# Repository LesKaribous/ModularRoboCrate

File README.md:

# ModularRoboCrate

Caisse de stockage et de déplacement pour nos robots et matériel de robotique. Rangements intérieur basés sur le système [GridFinity](https://gridfinity.xyz).

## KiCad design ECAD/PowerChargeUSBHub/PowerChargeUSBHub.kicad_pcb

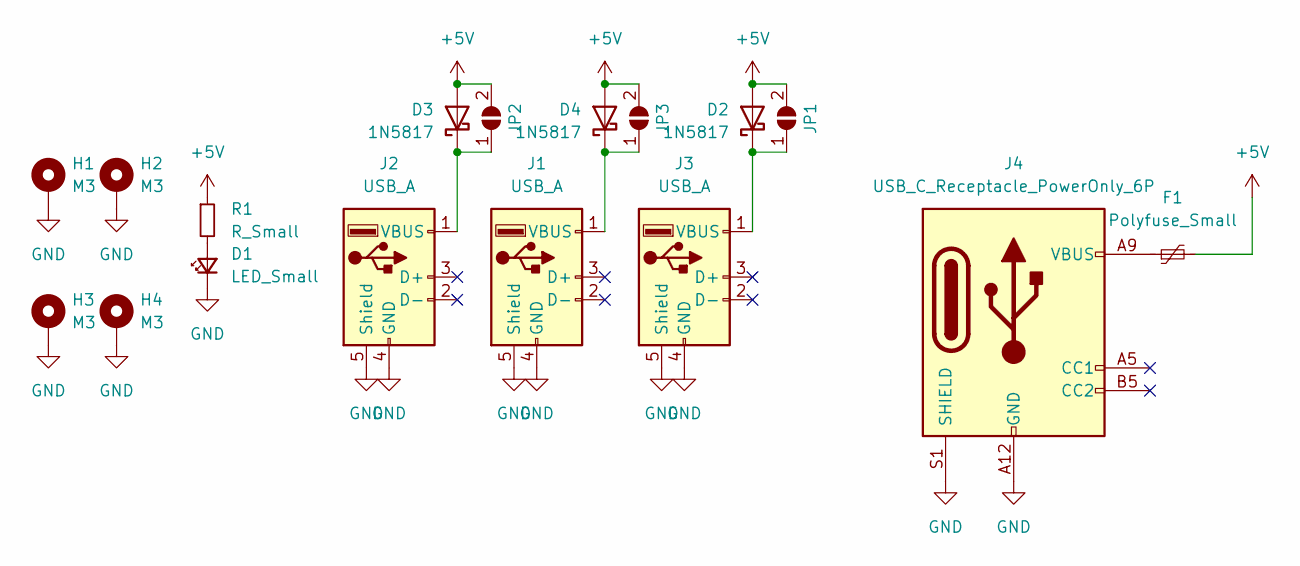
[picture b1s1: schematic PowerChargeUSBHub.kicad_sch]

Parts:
D1: LED_Small; LED_D5.0mm_Horizontal_O1.27mm_Z3.0mm
D2, D3, D4: 1N5817; D_DO-41_SOD81_P10.16mm_Horizontal
F1: Polyfuse_Small; Fuse_Littelfuse-LVR200
H1, H2, H3, H4: M3; MountingHole_3.2mm_M3_Pad_Via
J1, J2, J3: USB_A; USB_A_Molex_67643_Horizontal
J4: USB_C_Receptacle_PowerOnly_6P; USB_C_Receptacle_GCT_USB4125-xx-x_6P_TopMnt_Horizontal
JP1, JP2, JP3: SolderJumper_2_Open; SolderJumper-2_P1.3mm_Open_Pad1.0x1.5mm
R1: R_Small; R_1206_3216Metric_Pad1.30x1.75mm_HandSolder

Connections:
+5V: D2.2 (A), D3.2 (A), D4.2 (A), F1.2, JP1.2 (B), JP2.2 (B), JP3.2 (B), R1.1
GND: D1.1 (K), H1.1, H2.1, H3.1, H4.1, J1.4 (GND), J1.5 (Shield), J2.4 (GND), J2.5 (Shield), J3.4 (GND), J3.5 (Shield), J4.A12 (GND), J4.B12 (GND), J4.S1 (SHIELD)
unnamed: D1.2 (A), R1.2
unnamed: D2.1 (K), J3.1 (VBUS), JP1.1 (A)
unnamed: D3.1 (K), J2.1 (VBUS), JP2.1 (A)
unnamed: D4.1 (K), J1.1 (VBUS), JP3.1 (A)
unnamed: F1.1, J4.A9 (VBUS), J4.B9 (VBUS)

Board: 2 copper layers, 17 parts (0 on the bottom side), 7 nets, no tracks yet.

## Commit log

2024-02-24 init repo with new and existing files
2024-02-24 update with jekyll
2024-02-24 Create docs
2024-02-24 change Docs name
2024-02-24 add exclusions
2024-02-24 add include cache
2024-02-25 WIP - first components
2024-02-25 Add usbn C and polyfuse
2024-02-25 Create Dock
2024-04-19 before Belgium
